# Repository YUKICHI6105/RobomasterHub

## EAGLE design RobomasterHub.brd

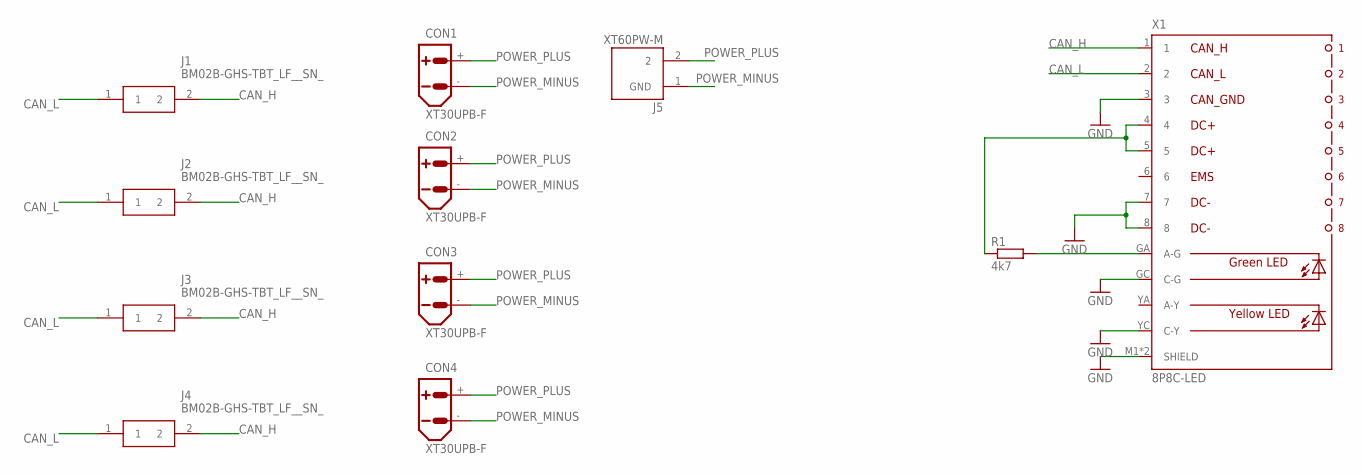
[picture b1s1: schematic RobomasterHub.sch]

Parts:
CON1, CON2, CON3, CON4: XT30UPB-F
J1, J2, J3, J4: BM02B-GHS-TBT_LF__SN_; BM02B-GHS-TBT_1
J5: XT60PW-M; AMASS_XT60PW-M
R1: 4k7; R0603
X1: 8P8C-LED

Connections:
CAN_H: J1.2, J2.2, J3.2, J4.2, X1.1
CAN_L: J1.1, J2.1, J3.1, J4.1, X1.2
GND: X1.3, X1.7, X1.8, X1.GC (C-G), X1.M1 (SHIELD), X1.M2 (SHIELD), X1.YC (C-Y)
unnamed: R1.2, X1.GA (A-G)
unnamed: R1.1, X1.4, X1.5
POWER_MINUS: CON1.-, CON2.-, CON3.-, CON4.-, J5.1 (GND)
POWER_PLUS: CON1.+, CON2.+, CON3.+, CON4.+, J5.2

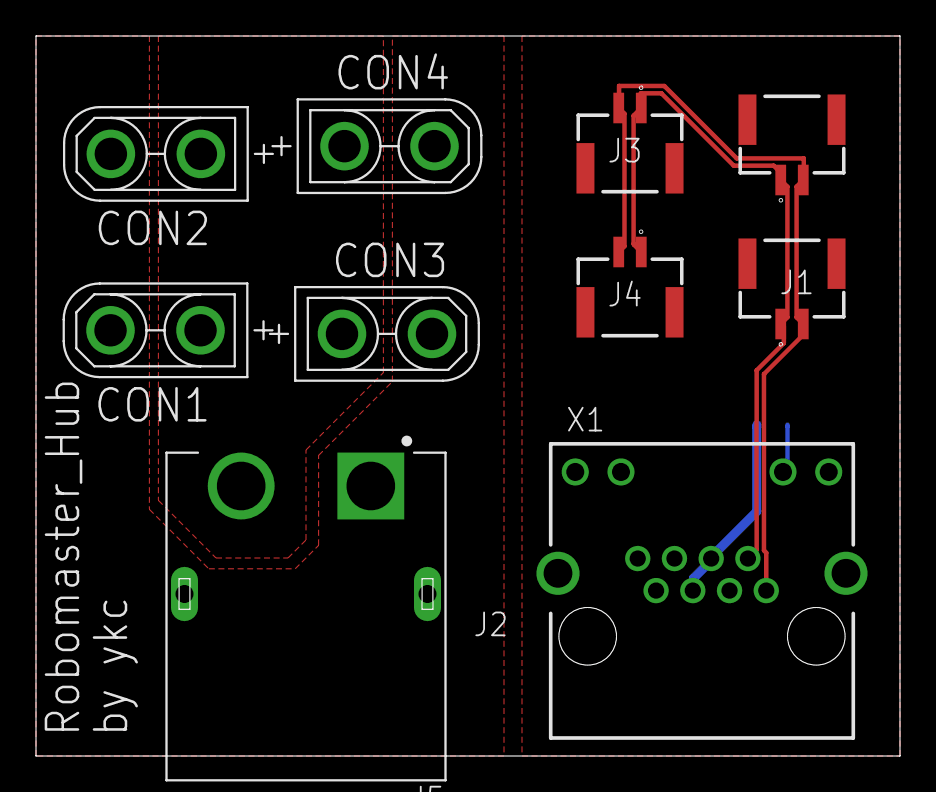
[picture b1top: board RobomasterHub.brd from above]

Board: 2 copper layers, 48.0 x 40.0 mm, 11 parts (1 on the bottom side), 7 nets.
